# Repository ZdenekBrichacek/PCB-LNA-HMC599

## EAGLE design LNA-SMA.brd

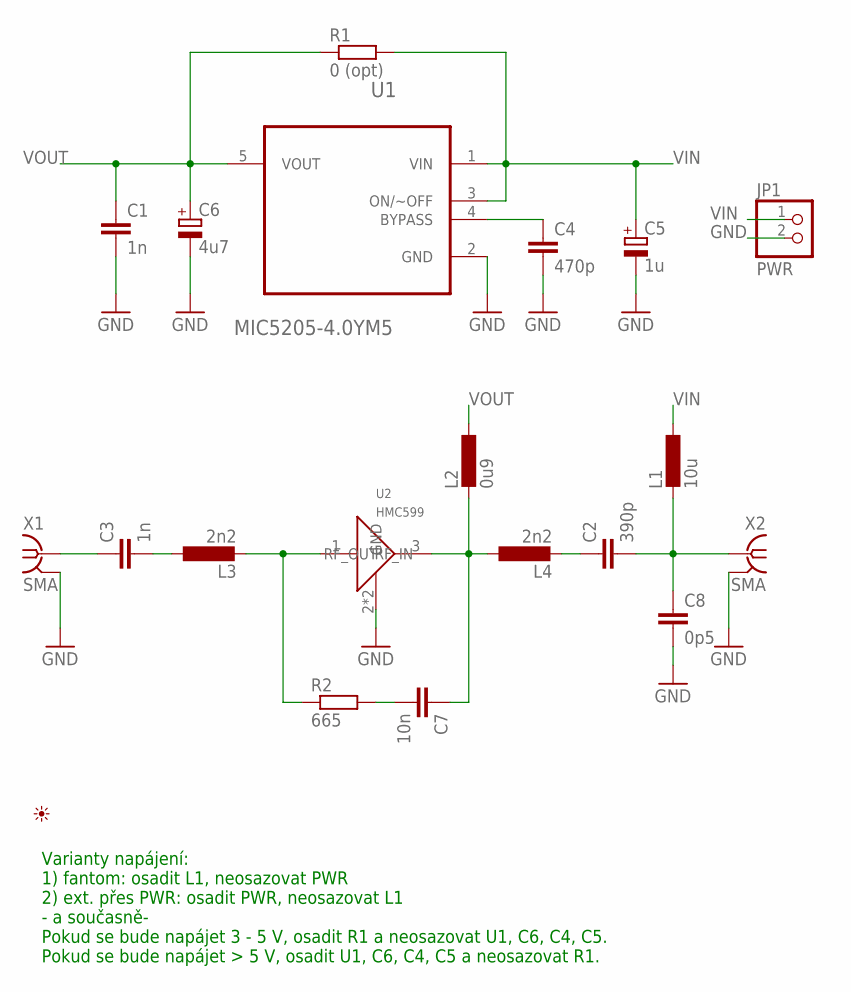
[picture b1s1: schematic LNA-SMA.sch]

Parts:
C1, C3: 1n; C0603
C2: 390p; C0603
C4: 470p; C0603
C5: 1u; SMC_A
C6: 4u7; SMC_A
C7: 10n; C0603
C8: 0p5; C0603
JP1: PWR; 1X02
L1: 10u; L2012C
L2: 0u9; L2012C
L3, L4: 2n2; L2012C
R1: 0 (opt); R0603
R2: 665; R0603
U1: MIC5205-4.0YM5; SOT95P280X145-5N
U2: HMC599; SOT89
U$1: PICTO_1
X1, X2: SMA; J502-ND-142-0701-801/806

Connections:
GND: C1.2, C4.2, C5.-, C6.-, C8.2, JP1.2, U1.2 (GND), U2.2 (GND), U2.2.1 (GND), X1.G@1 (2), X1.G@2 (2), X1.G@3 (2), X1.G@4 (2), X2.G@1 (2), X2.G@2 (2), X2.G@3 (2), X2.G@4 (2)
unnamed: C4.1, U1.4 (BYPASS)
unnamed: C3.2, L3.1
unnamed: C2.1, L4.2
unnamed: L3.2, R2.1, U2.1 (RF_IN)
unnamed: C7.1, L2.2, L4.1, U2.3 (RF_OUT)
unnamed: C7.2, R2.2
RF_IN: C2.2, C8.1, L1.2, X2.1
RF_OUT: C3.1, X1.1
VIN: C5.+, JP1.1, L1.1, R1.2, U1.1 (VIN), U1.3 (ON/~OFF)
VOUT: C1.1, C6.+, L2.1, R1.1, U1.5 (VOUT)

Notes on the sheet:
Varianty napájení: 1) fantom: osadit L1, neosazovat PWR 2) ext. přes PWR: osadit PWR, neosazovat L1 - a současně- Pokud se bude napájet 3 - 5 V, osadit R1 a neosazovat U1, C6, C4, C5. Pokud se bude napájet > 5 V, osadit U1, C6, C4, C5 a neosazovat R1.

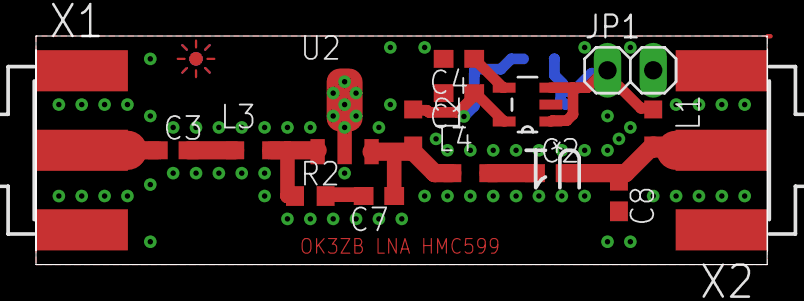
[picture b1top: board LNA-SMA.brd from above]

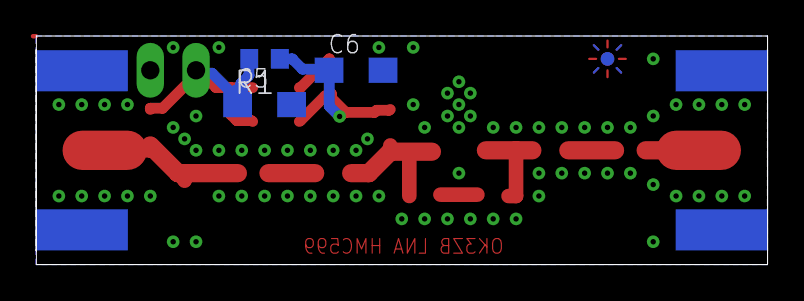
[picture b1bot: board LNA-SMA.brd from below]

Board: 2 copper layers, 40.6 x 12.7 mm, 20 parts (3 on the bottom side), 11 nets.

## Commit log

2017-10-10 :tada: Added .gitattributes & .gitignore files
2017-10-10 Initial version
